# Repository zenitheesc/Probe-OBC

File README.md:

<h1 align="center" style="color:white; background-color:black">Probe-OBC</h1>
<h4 align="center">On-Board Computer for stratospheric probes, using Zenith Stack</h4>

<p align="center">

</p>

<p align="center">
    <a href="#environment-and-tools">Environment and Tools</a> •
    <a href="#z-hub">Z-Hub</a> •
    <a href="#matias-obc">Matias OBC</a>
</p>

This configuration of the Eletrical power system requires a board that monitors the charger and battery, in addition to performing thermal control.

## Environment and tools

This system was designed using Eagle v.9.4.2

## Z-Hub

<a href="https://github.com/zenitheesc/Probe-OBC/tree/main/Hardware/Matias_OBC-v.3.0"><h2>Matias OBC</h2></a>

---

<p align="center">

</p>
<p align = "center">
<a href="zenith.eesc@gmail.com">zenith.eesc@gmail.com</a>
</p>

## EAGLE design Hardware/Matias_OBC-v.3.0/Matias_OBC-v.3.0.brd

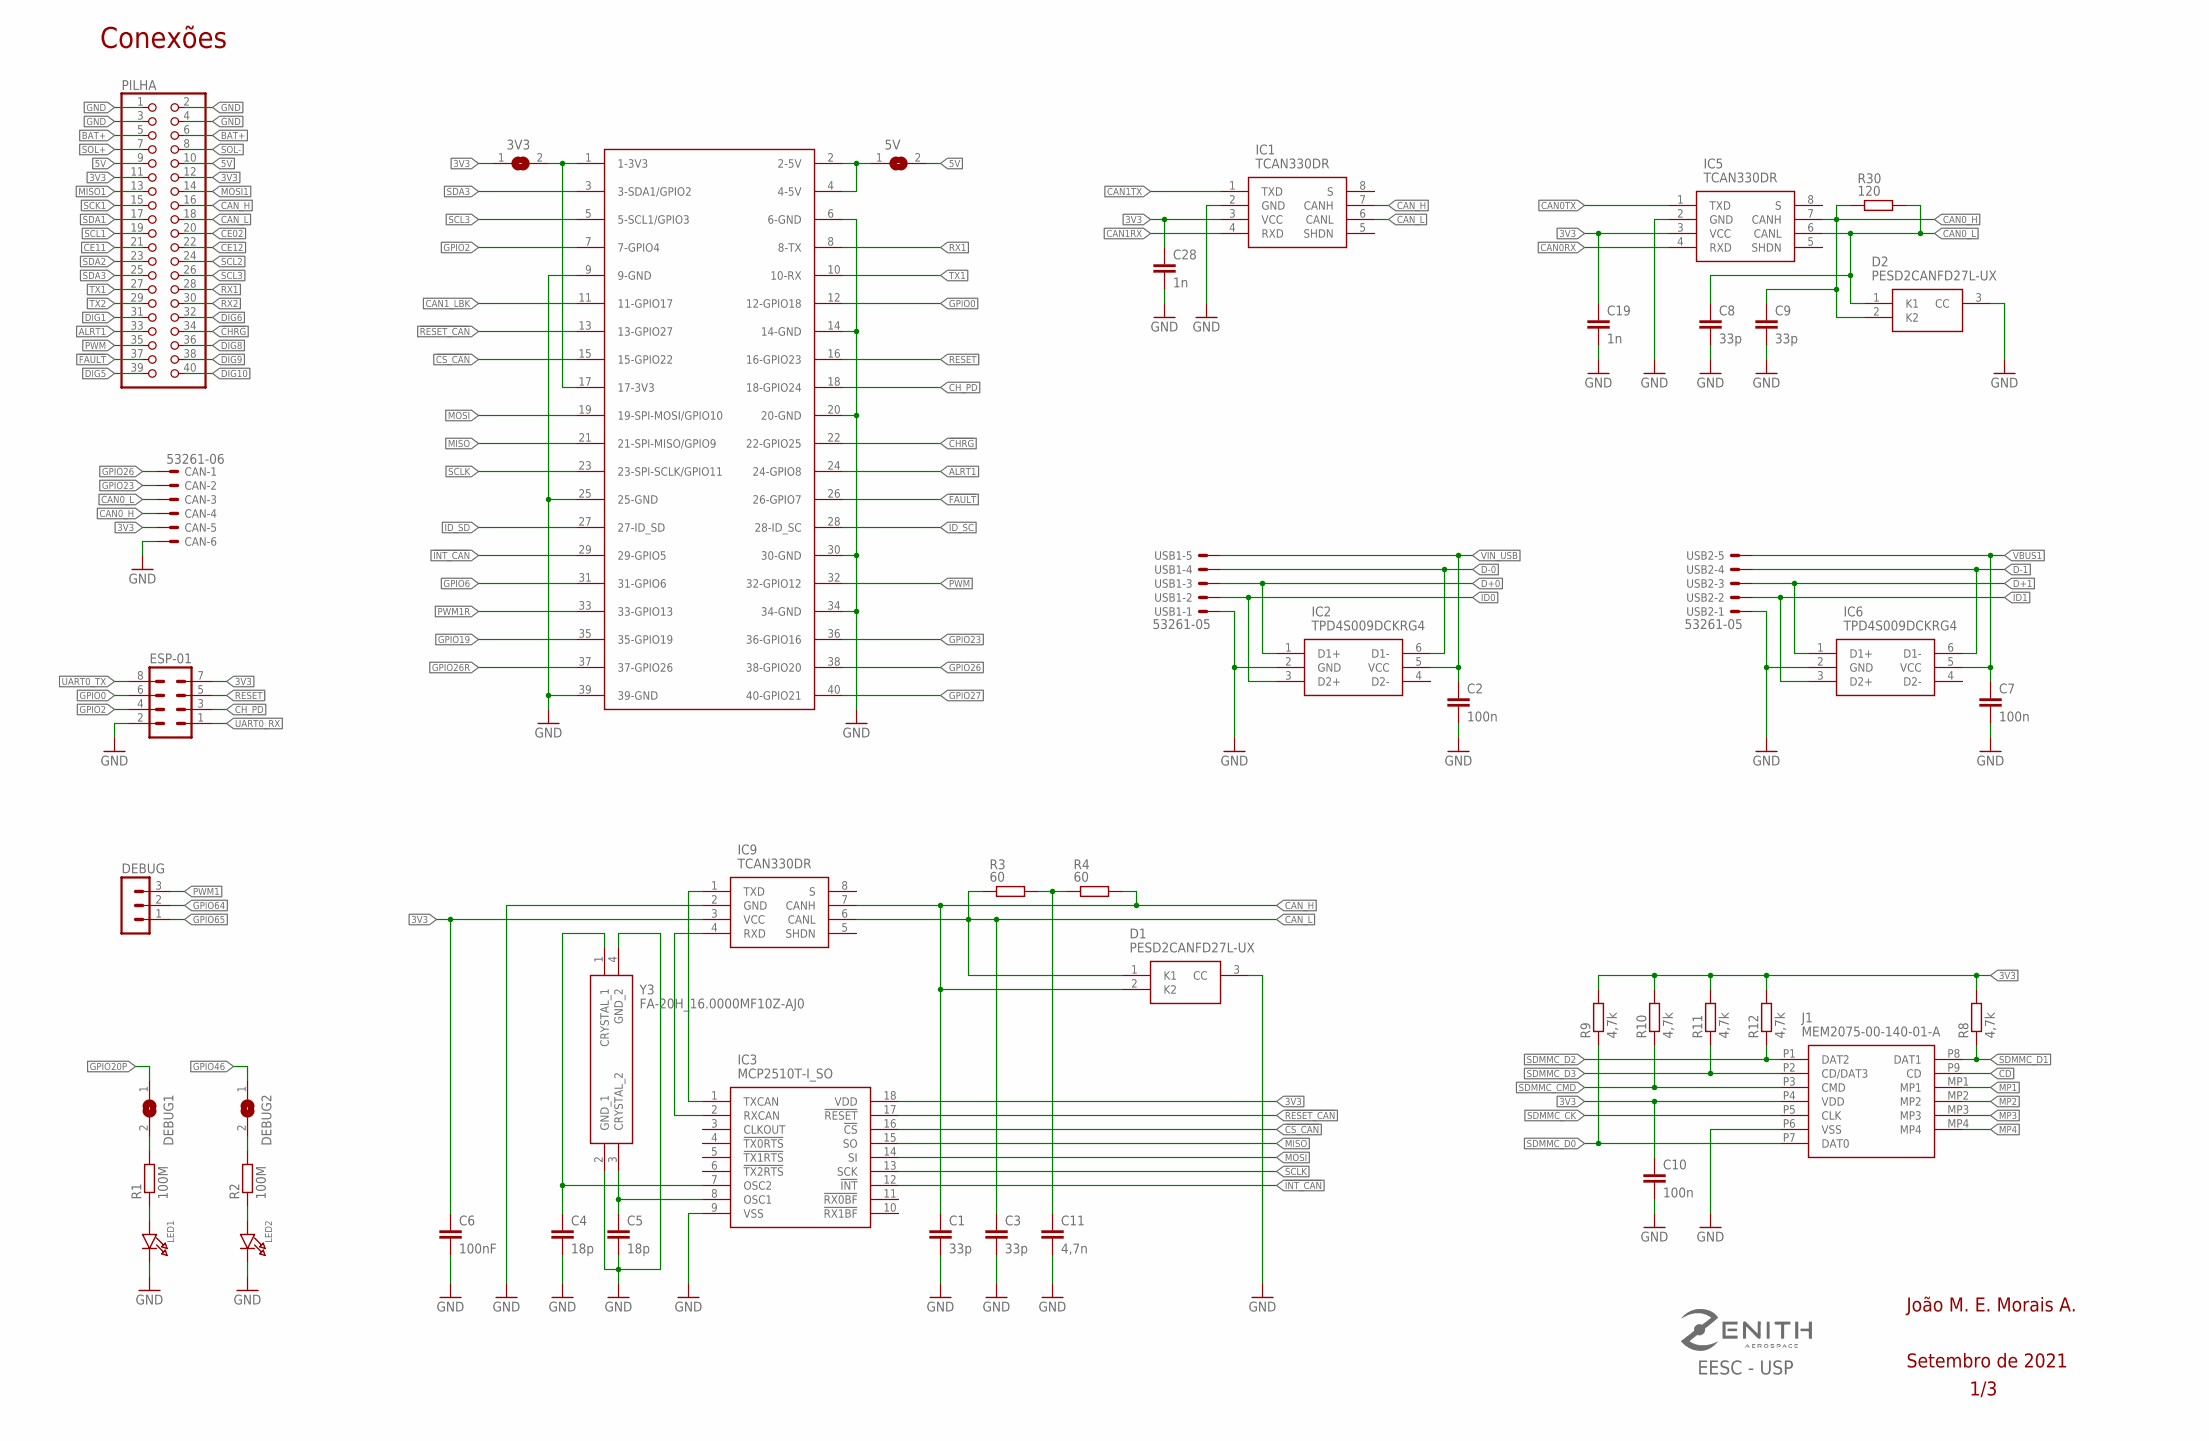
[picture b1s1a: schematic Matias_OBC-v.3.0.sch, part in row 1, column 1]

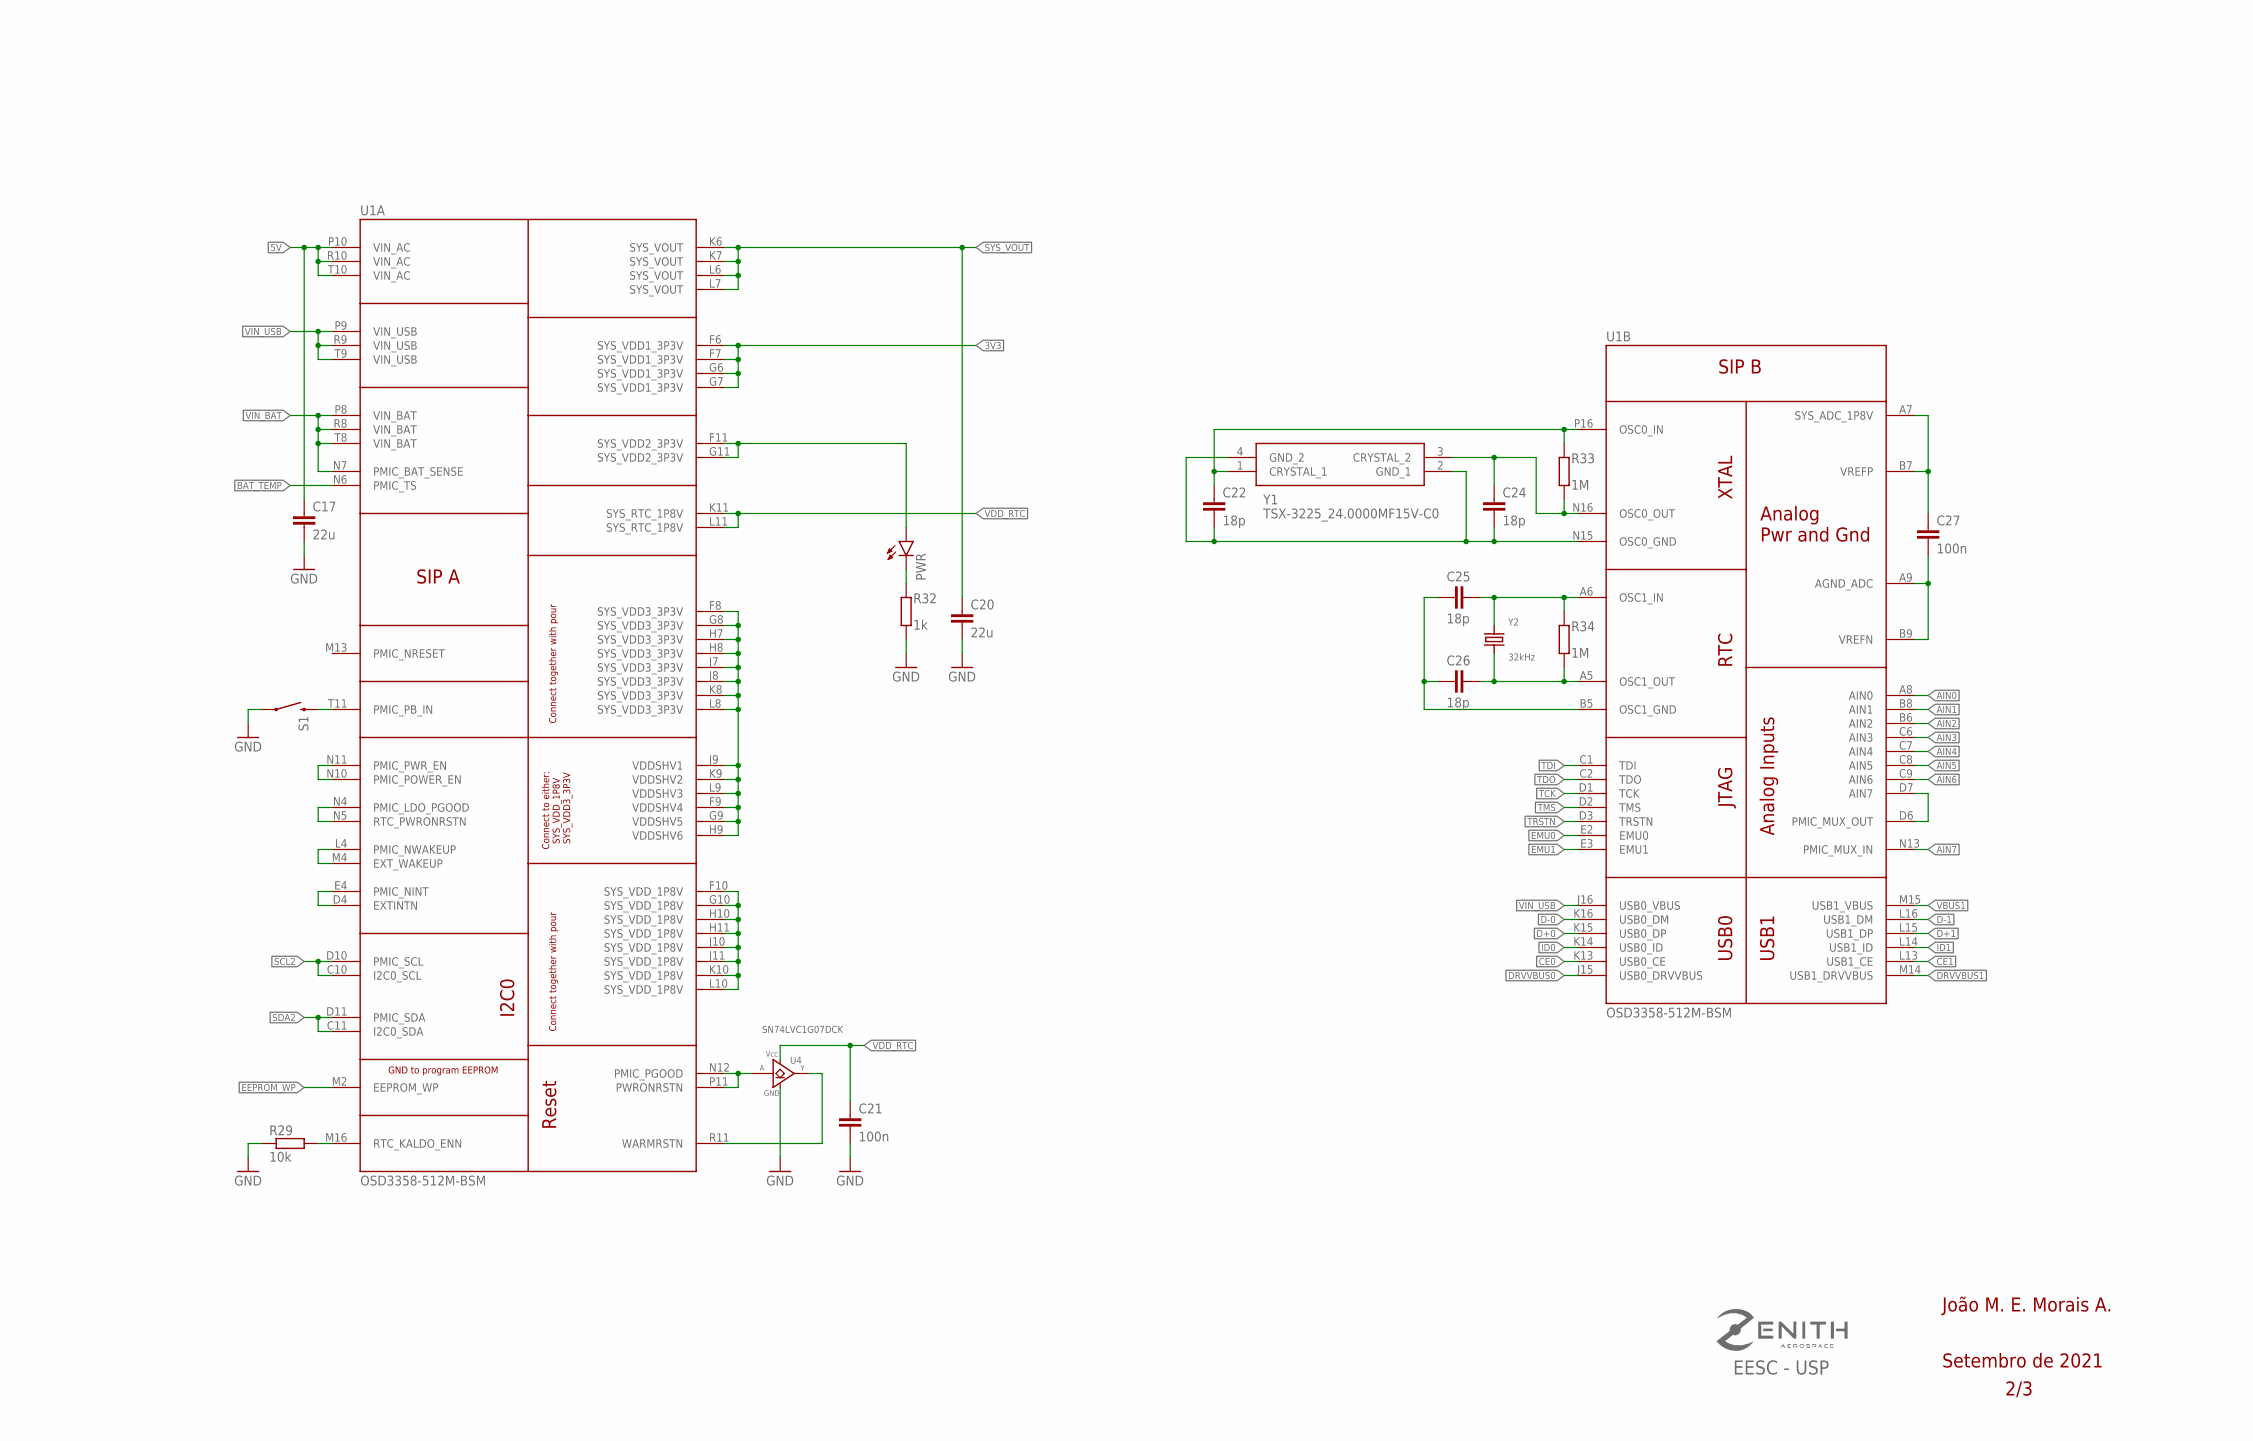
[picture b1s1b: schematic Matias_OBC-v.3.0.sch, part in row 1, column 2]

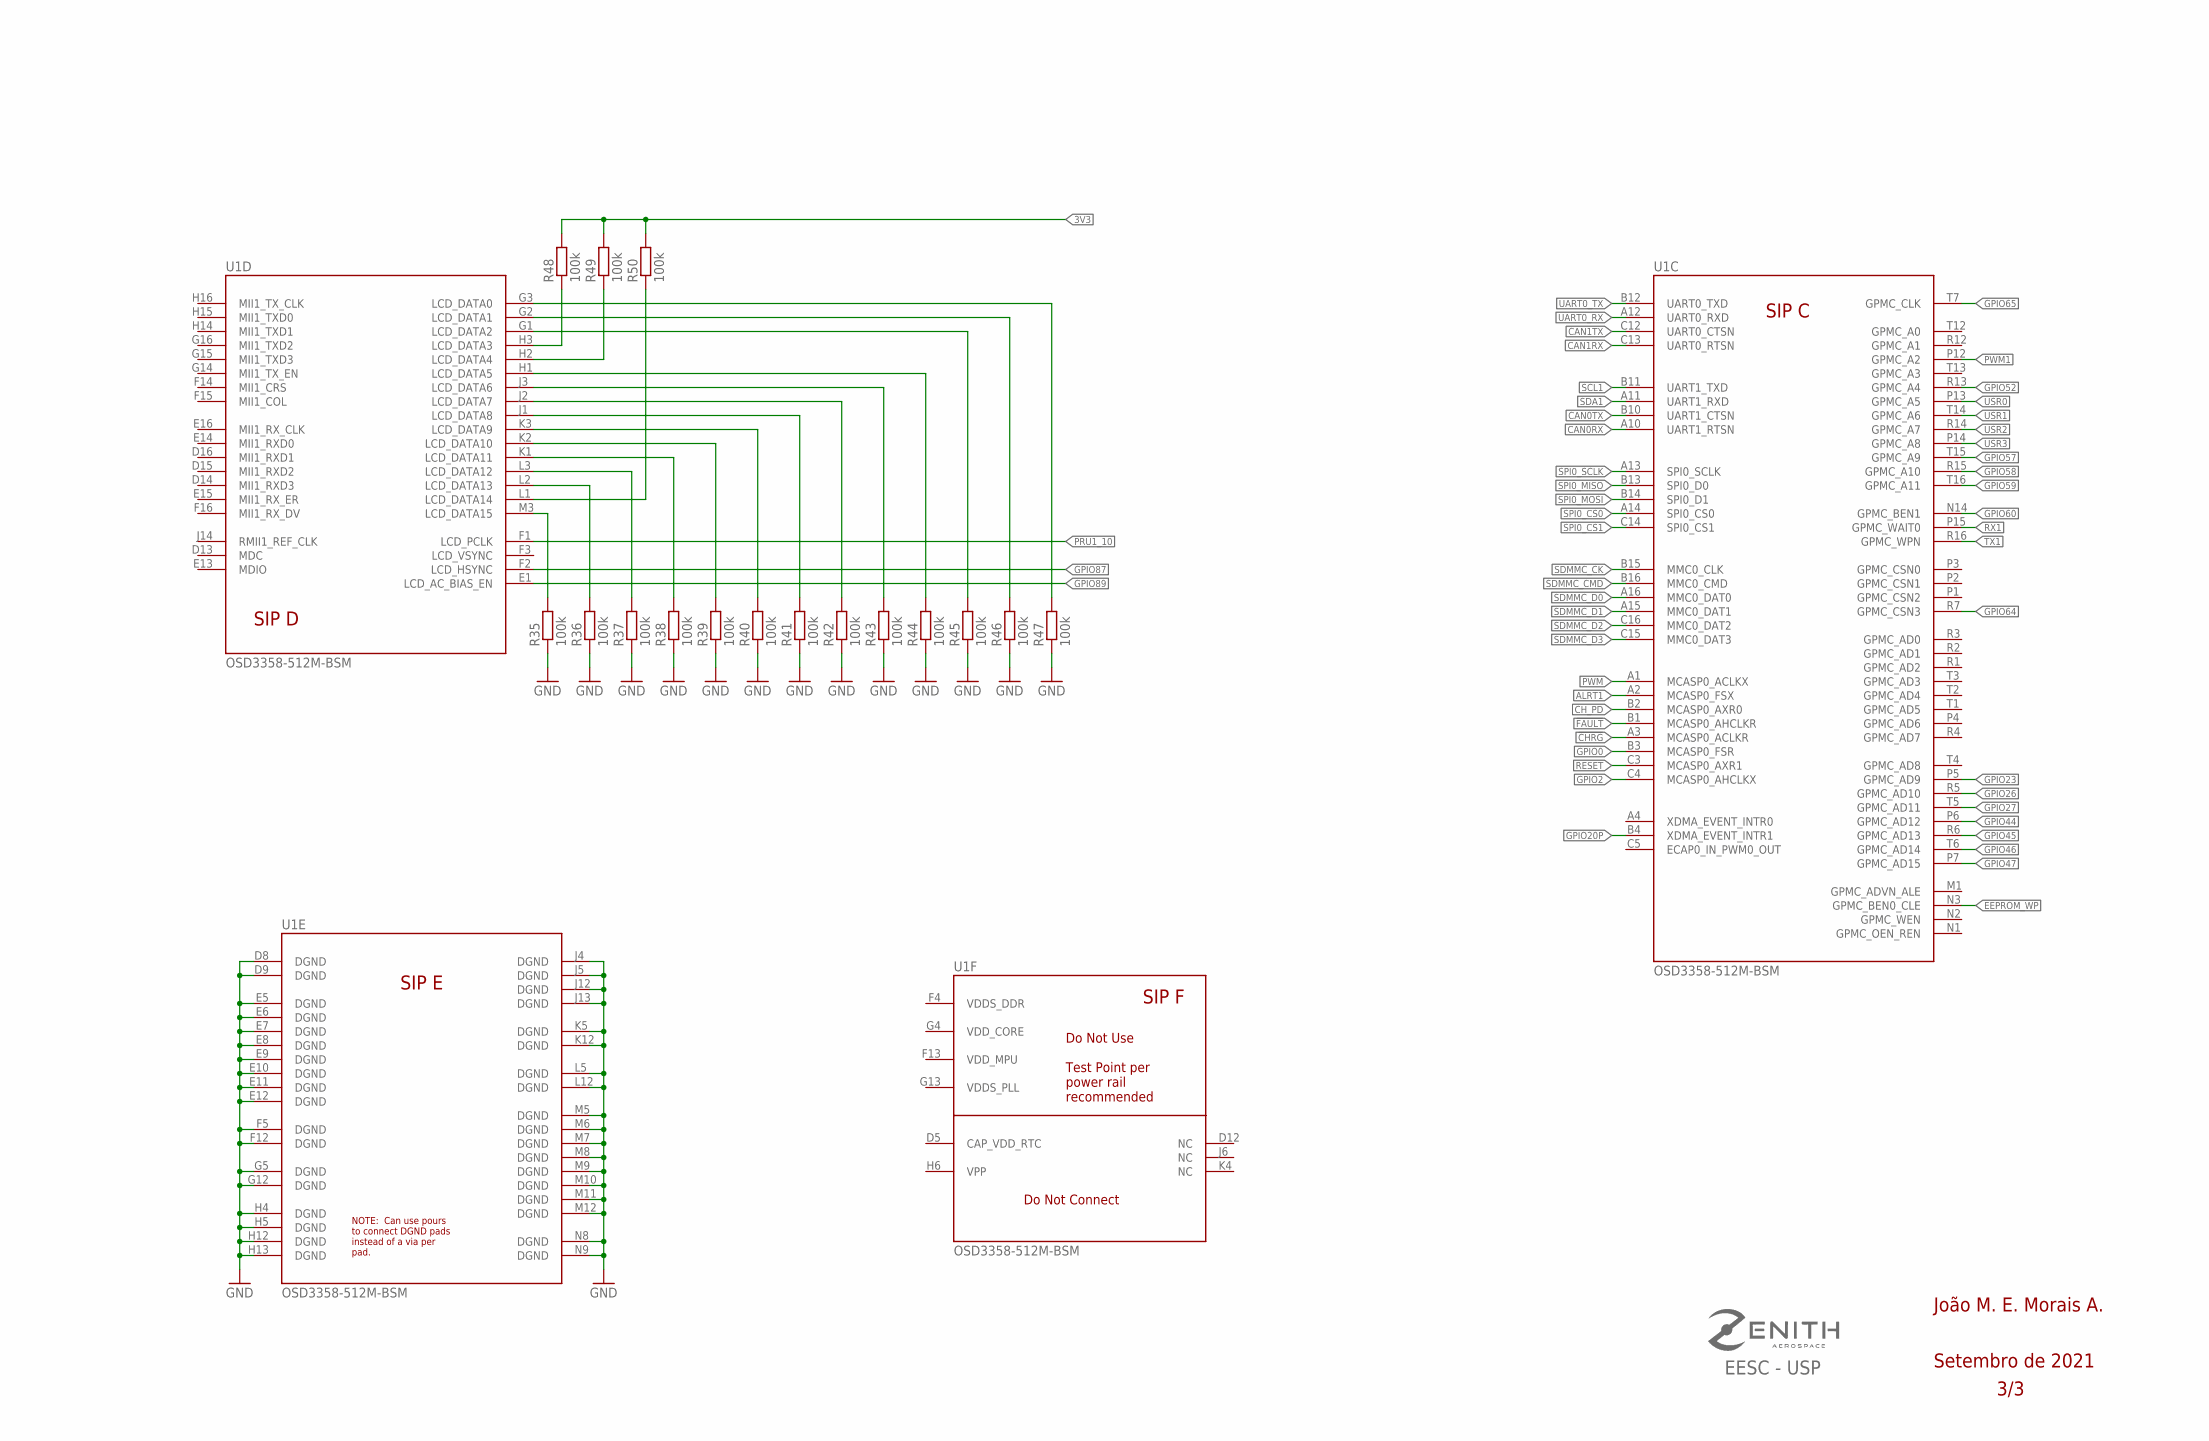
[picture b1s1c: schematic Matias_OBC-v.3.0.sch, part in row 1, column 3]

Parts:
3V3, 5V: SJ
C1, C3, C8, C9: 33p; C0805
C2, C7, C10, C21, C27: 100n; C0805
C4, C5, C22, C24, C25, C26: 18p; C0805
C6: 100nF; C0805
C11: 4,7n; C0805
C17, C20: 22u; C0805
C19, C28: 1n; C0805
CAN: 53261-06
D1, D2: PESD2CANFD27L-UX; SOT65P210X110-3N
DEBUG: MA03-1
DEBUG1, DEBUG2: SOLDERJUMPERREFLOW_NOPASTE; SOLDERJUMPER_REFLOW_NOPASTE
ESP-01: MA04-2
IC1, IC5, IC9: TCAN330DR; SOIC127P600X175-8N
IC2, IC6: TPD4S009DCKRG4; SOT65P210X110-6N
IC3: MCP2510T-I_SO; SOIC127P1030X265-18N
J1: MEM2075-00-140-01-A; MEM20750014001A
LED1, LED2: LED1206; CHIPLED_1206
PILHA: PINHD-2X20; 2X20
PWR: LEDCHIP-LED0805; CHIP-LED0805
R1, R2: 100M; R0805
R3, R4: 60; R0805
R8, R9, R10, R11, R12: 4,7k; R0805
R29: 10k; R0805
R30: 120; R0805
R32: 1k; R0805
R33, R34: 1M; R0805
R35, R36, R37, R38, R39, R40, R41, R42, R43, R44, R45, R46, R47, R48, R49, R50: 100k; R0805
S1: MOMENTARY-SWITCH-SPST-SMD-6.0X3.5MM; TACTILE_SWITCH_SMD_6.0X3.5MM
U1: OSD3358-512M-BSM; OSD335X-BGA-256
U2: RASPBERRY-PI+PIZERO; RASPBERRY-PI-ZERO
U4: SN74LVC1G07DCK; SC70(TI-DCK)
USB1, USB2: 53261-05
Y1: TSX-3225_24.0000MF15V-C0; TSX3225240000MF15VC0
Y2: 32kHz; CRYSTAL_8X3.8
Y3: FA-20H_16.0000MF10Z-AJ0; FA20H160000MF12ZAC3

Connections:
3V3: 3V3.1, C6.1, C10.1, C19.1, C28.1, CAN.5, ESP-01.7, IC1.3 (VCC), IC3.18 (VDD), IC5.3 (VCC), IC9.3 (VCC), J1.P4 (VDD), PILHA.11, PILHA.12, R8.2, R9.2, R10.2, R11.2, R12.2, R48.2, R49.2, R50.2, U1.F6 (SYS_VDD1_3P3V), U1.F7 (SYS_VDD1_3P3V), U1.G6 (SYS_VDD1_3P3V), U1.G7 (SYS_VDD1_3P3V)
5V: 5V.2, C17.1, PILHA.9, PILHA.10, U1.P10 (VIN_AC), U1.R10 (VIN_AC), U1.T10 (VIN_AC)
!CHRG: PILHA.34, U1.A3 (MCASP0_ACLKR), U2.22 (22-GPIO25)
!CS_CAN: IC3.16 (!CS), U2.15 (15-GPIO22)
!FAULT: PILHA.37, U1.B1 (MCASP0_AHCLKR), U2.26 (26-GPIO7)
!INT_CAN: IC3.12 (!INT), U2.29 (29-GPIO5)
!RESET_CAN: IC3.17 (!RESET), U2.13 (13-GPIO27)
AIN0: U1.A8 (AIN0)
AIN1: U1.B8 (AIN1)
AIN2: U1.B6 (AIN2)
AIN3: U1.C6 (AIN3)
AIN4: U1.C7 (AIN4)
AIN5: U1.C8 (AIN5)
AIN6: U1.C9 (AIN6)
AIN7: U1.N13 (PMIC_MUX_IN)
ALRT1: PILHA.33, U1.A2 (MCASP0_FSX), U2.24 (24-GPIO8)
BAT+: PILHA.5, PILHA.6
BAT_TEMP: U1.N6 (PMIC_TS)
CAN0RX: IC5.4 (RXD), U1.A10 (UART1_RTSN)
CAN0TX: IC5.1 (TXD), U1.B10 (UART1_CTSN)
CAN0_H: C9.1, CAN.4, D2.2 (K2), IC5.7 (CANH), R30.1
CAN0_L: C8.1, CAN.3, D2.1 (K1), IC5.6 (CANL), R30.2
CAN1RX: IC1.4 (RXD), U1.C13 (UART0_RTSN)
CAN1TX: IC1.1 (TXD), U1.C12 (UART0_CTSN)
CAN1_LBK: U2.11 (11-GPIO17)
CAN_H: C1.1, D1.2 (K2), IC1.7 (CANH), IC9.7 (CANH), PILHA.16, R4.1
CAN_L: C3.1, D1.1 (K1), IC1.6 (CANL), IC9.6 (CANL), PILHA.18, R3.2
CD: J1.P9 (CD)
CE0: U1.K13 (USB0_CE)
CE1: U1.L13 (USB1_CE)
CE02: PILHA.20
CE11: PILHA.21
CE12: PILHA.22
CH_PD: ESP-01.3, U1.B2 (MCASP0_AXR0), U2.18 (18-GPIO24)
D+0: IC2.1 (D1+), U1.K15 (USB0_DP), USB1.3
D+1: IC6.1 (D1+), U1.L15 (USB1_DP), USB2.3
D-0: IC2.6 (D1-), U1.K16 (USB0_DM), USB1.4
D-1: IC6.6 (D1-), U1.L16 (USB1_DM), USB2.4
DIG1: PILHA.31
DIG5: PILHA.39
DIG6: PILHA.32
DIG8: PILHA.36
DIG9: PILHA.38
DIG10: PILHA.40
DRVVBUS0: U1.J15 (USB0_DRVVBUS)
DRVVBUS1: U1.M14 (USB1_DRVVBUS)
EEPROM_WP: U1.M2 (EEPROM_WP), U1.N3 (GPMC_BEN0_CLE)
EMU0: U1.E2 (EMU0)
EMU1: U1.E3 (EMU1)
GND: C1.2, C2.2, C3.2, C4.2, C5.2, C6.2, C7.2, C8.2, C9.2, C10.2, C11.2, C17.2, C19.2, C20.2, C21.2, C28.2, CAN.6, D1.3 (CC), D2.3 (CC), ESP-01.2, IC1.2 (GND), IC2.2 (GND), IC3.9 (VSS), IC5.2 (GND), IC6.2 (GND), IC9.2 (GND), J1.P6 (VSS), LED1.C, LED2.C, PILHA.1, PILHA.2, PILHA.3, PILHA.4, R29.1, R32.1, R35.1, R36.1, R37.1, R38.1, R39.1, R40.1, R41.1, R42.1, R43.1, R44.1, R45.1, R46.1, R47.1, S1.1, U1.D8 (DGND), U1.D9 (DGND), U1.E5 (DGND), U1.E6 (DGND), U1.E7 (DGND), U1.E8 (DGND), U1.E9 (DGND), U1.E10 (DGND), U1.E11 (DGND), U1.E12 (DGND), U1.F5 (DGND), U1.F12 (DGND), U1.G5 (DGND), U1.G12 (DGND), U1.H4 (DGND), U1.H5 (DGND), U1.H12 (DGND), U1.H13 (DGND), U1.J4 (DGND), U1.J5 (DGND), U1.J12 (DGND), U1.J13 (DGND), U1.K5 (DGND), U1.K12 (DGND), U1.L5 (DGND), U1.L12 (DGND), U1.M5 (DGND), U1.M6 (DGND), U1.M7 (DGND), U1.M8 (DGND), U1.M9 (DGND), U1.M10 (DGND), U1.M11 (DGND), U1.M12 (DGND), U1.N8 (DGND), U1.N9 (DGND), U2.6 (6-GND), U2.9 (9-GND), U2.14 (14-GND), U2.20 (20-GND), U2.25 (25-GND), U2.30 (30-GND), U2.34 (34-GND), U2.39 (39-GND), U4.3 (GND), USB1.1, USB2.1, Y3.2 (GND_1), Y3.4 (GND_2)
GPIO0: ESP-01.6, U1.B3 (MCASP0_FSR), U2.12 (12-GPIO18)
GPIO2: ESP-01.4, U1.C4 (MCASP0_AHCLKX), U2.7 (7-GPIO4)
GPIO6: U2.31 (31-GPIO6)
GPIO19: U2.35 (35-GPIO19)
GPIO20P: DEBUG1.1, U1.B4 (XDMA_EVENT_INTR1)
GPIO23: CAN.2, U1.P5 (GPMC_AD9), U2.36 (36-GPIO16)
GPIO26: CAN.1, U1.R5 (GPMC_AD10), U2.38 (38-GPIO20)
GPIO26R: U2.37 (37-GPIO26)
GPIO27: U1.T5 (GPMC_AD11), U2.40 (40-GPIO21)
GPIO44: U1.P6 (GPMC_AD12)
GPIO45: U1.R6 (GPMC_AD13)
GPIO46: DEBUG2.1, U1.T6 (GPMC_AD14)
GPIO47: U1.P7 (GPMC_AD15)
GPIO52: U1.R13 (GPMC_A4)
GPIO57: U1.T15 (GPMC_A9)
GPIO58: U1.R15 (GPMC_A10)
GPIO59: U1.T16 (GPMC_A11)
GPIO60: U1.N14 (GPMC_BEN1)
GPIO64: DEBUG.2, U1.R7 (GPMC_CSN3)
GPIO65: DEBUG.1, U1.T7 (GPMC_CLK)
GPIO87: U1.F2 (LCD_HSYNC)
GPIO89: U1.E1 (LCD_AC_BIAS_EN)
ID0: IC2.3 (D2+), U1.K14 (USB0_ID), USB1.2
ID1: IC6.3 (D2+), U1.L14 (USB1_ID), USB2.2
ID_SC: U2.28 (28-ID_SC)
ID_SD: U2.27 (27-ID_SD)
MISO: IC3.15 (SO), U2.21 (21-SPI-MISO/GPIO9)
MISO1: PILHA.13
MOSI: IC3.14 (SI), U2.19 (19-SPI-MOSI/GPIO10)
MOSI1: PILHA.14
MP1: J1.MP1
MP2: J1.MP2
MP3: J1.MP3
MP4: J1.MP4
unnamed: LED1.A, R1.1
unnamed: 5V.1, U2.2 (2-5V), U2.4 (4-5V)
unnamed: 3V3.2, U2.1 (1-3V3), U2.17 (17-3V3)
unnamed: C11.1, R3.1, R4.2
unnamed: LED2.A, R2.1
unnamed: DEBUG1.2, R1.2
unnamed: DEBUG2.2, R2.2
unnamed: C5.1, IC3.8 (OSC1), Y3.3 (CRYSTAL_2)
unnamed: C4.1, IC3.7 (OSC2), Y3.1 (CRYSTAL_1)
unnamed: S1.2, U1.T11 (PMIC_PB_IN)
unnamed: U1.N10 (PMIC_POWER_EN), U1.N11 (PMIC_PWR_EN)
unnamed: U1.N4 (PMIC_LDO_PGOOD), U1.N5 (RTC_PWRONRSTN)
unnamed: U1.L4 (PMIC_NWAKEUP), U1.M4 (EXT_WAKEUP)
unnamed: U1.D4 (EXTINTN), U1.E4 (PMIC_NINT)
unnamed: R29.2, U1.M16 (RTC_KALDO_ENN)
unnamed: PWR.A, U1.F11 (SYS_VDD2_3P3V), U1.G11 (SYS_VDD2_3P3V)
unnamed: PWR.C, R32.2
unnamed: U1.F8 (SYS_VDD3_3P3V), U1.F9 (VDDSHV4), U1.G8 (SYS_VDD3_3P3V), U1.G9 (VDDSHV5), U1.H7 (SYS_VDD3_3P3V), U1.H8 (SYS_VDD3_3P3V), U1.H9 (VDDSHV6), U1.J7 (SYS_VDD3_3P3V), U1.J8 (SYS_VDD3_3P3V), U1.J9 (VDDSHV1), U1.K8 (SYS_VDD3_3P3V), U1.K9 (VDDSHV2), U1.L8 (SYS_VDD3_3P3V), U1.L9 (VDDSHV3)
unnamed: U1.F10 (SYS_VDD_1P8V), U1.G10 (SYS_VDD_1P8V), U1.H10 (SYS_VDD_1P8V), U1.H11 (SYS_VDD_1P8V), U1.J10 (SYS_VDD_1P8V), U1.J11 (SYS_VDD_1P8V), U1.K10 (SYS_VDD_1P8V), U1.L10 (SYS_VDD_1P8V)
unnamed: U1.N12 (PMIC_PGOOD), U1.P11 (PWRONRSTN), U4.2 (A)
unnamed: U1.R11 (WARMRSTN), U4.4 (Y)
unnamed: C22.1, R33.2, U1.P16 (OSC0_IN), Y1.1 (CRYSTAL_1)
unnamed: C24.1, R33.1, U1.N16 (OSC0_OUT), Y1.3 (CRYSTAL_2)
unnamed: C22.2, C24.2, U1.N15 (OSC0_GND), Y1.2 (GND_1), Y1.4 (GND_2)
unnamed: C26.1, R34.1, U1.A5 (OSC1_OUT), Y2.P$4 (2)
unnamed: C25.1, R34.2, U1.A6 (OSC1_IN), Y2.P$1 (1)
unnamed: C25.2, C26.2, U1.B5 (OSC1_GND)
unnamed: U1.D6 (PMIC_MUX_OUT), U1.D7 (AIN7)
unnamed: C27.2, U1.A9 (AGND_ADC), U1.B9 (VREFN)
unnamed: C27.1, U1.A7 (SYS_ADC_1P8V), U1.B7 (VREFP)
unnamed: R35.2, U1.M3 (LCD_DATA15)
unnamed: R36.2, U1.L2 (LCD_DATA13)
unnamed: R37.2, U1.L3 (LCD_DATA12)
unnamed: R38.2, U1.K1 (LCD_DATA11)
unnamed: R39.2, U1.K2 (LCD_DATA10)
unnamed: R40.2, U1.K3 (LCD_DATA9)
unnamed: R41.2, U1.J1 (LCD_DATA8)
unnamed: R42.2, U1.J2 (LCD_DATA7)
unnamed: R43.2, U1.J3 (LCD_DATA6)
unnamed: R44.2, U1.H1 (LCD_DATA5)
unnamed: R45.2, U1.G1 (LCD_DATA2)
unnamed: R46.2, U1.G2 (LCD_DATA1)
unnamed: R47.2, U1.G3 (LCD_DATA0)
unnamed: R48.1, U1.H3 (LCD_DATA3)
unnamed: R49.1, U1.H2 (LCD_DATA4)
unnamed: R50.1, U1.L1 (LCD_DATA14)
PRU1_10: U1.F1 (LCD_PCLK)
PWM: PILHA.35, U1.A1 (MCASP0_ACLKX), U2.32 (32-GPIO12)
PWM1: DEBUG.3, U1.P12 (GPMC_A2)
PWM1R: U2.33 (33-GPIO13)
RESET: ESP-01.5, U1.C3 (MCASP0_AXR1), U2.16 (16-GPIO23)
RX1: PILHA.28, U1.P15 (GPMC_WAIT0), U2.8 (8-TX)
RX2: PILHA.30
RXCAN1: IC3.2 (RXCAN), IC9.4 (RXD)
SCK1: PILHA.15
SCL1: PILHA.19, U1.B11 (UART1_TXD)
SCL2: PILHA.24, U1.C10 (I2C0_SCL), U1.D10 (PMIC_SCL)
SCL3: PILHA.26, U2.5 (5-SCL1/GPIO3)
SCLK: IC3.13 (SCK), U2.23 (23-SPI-SCLK/GPIO11)
SDA1: PILHA.17, U1.A11 (UART1_RXD)
SDA2: PILHA.23, U1.C11 (I2C0_SDA), U1.D11 (PMIC_SDA)
SDA3: PILHA.25, U2.3 (3-SDA1/GPIO2)
SDMMC_CK: J1.P5 (CLK), U1.B15 (MMC0_CLK)
SDMMC_CMD: J1.P3 (CMD), R10.1, U1.B16 (MMC0_CMD)
SDMMC_D0: J1.P7 (DAT0), R9.1, U1.A16 (MMC0_DAT0)
SDMMC_D1: J1.P8 (DAT1), R8.1, U1.A15 (MMC0_DAT1)
SDMMC_D2: J1.P1 (DAT2), R12.1, U1.C16 (MMC0_DAT2)
SDMMC_D3: J1.P2 (CD/DAT3), R11.1, U1.C15 (MMC0_DAT3)
SOL+: PILHA.7
SOL-: PILHA.8
SPI0_CS0: U1.A14 (SPI0_CS0)
SPI0_CS1: U1.C14 (SPI0_CS1)
SPI0_MISO: U1.B13 (SPI0_D0)
SPI0_MOSI: U1.B14 (SPI0_D1)
SPI0_SCLK: U1.A13 (SPI0_SCLK)
SYS_VOUT: C20.1, U1.K6 (SYS_VOUT), U1.K7 (SYS_VOUT), U1.L6 (SYS_VOUT), U1.L7 (SYS_VOUT)
TCK: U1.D1 (TCK)
TDI: U1.C1 (TDI)
TDO: U1.C2 (TDO)
TMS: U1.D2 (TMS)
TRSTN: U1.D3 (TRSTN)
TX1: PILHA.27, U1.R16 (GPMC_WPN), U2.10 (10-RX)
TX2: PILHA.29
TXCAN1: IC3.1 (TXCAN), IC9.1 (TXD)
UART0_RX: ESP-01.1, U1.A12 (UART0_RXD)
UART0_TX: ESP-01.8, U1.B12 (UART0_TXD)
USR0: U1.P13 (GPMC_A5)
USR1: U1.T14 (GPMC_A6)
USR2: U1.R14 (GPMC_A7)
USR3: U1.P14 (GPMC_A8)
VBUS1: C7.1, IC6.5 (VCC), U1.M15 (USB1_VBUS), USB2.5
VDD_RTC: C21.1, U1.K11 (SYS_RTC_1P8V), U1.L11 (SYS_RTC_1P8V), U4.5 (VCC)
VIN_BAT: U1.N7 (PMIC_BAT_SENSE), U1.P8 (VIN_BAT), U1.R8 (VIN_BAT), U1.T8 (VIN_BAT)
VIN_USB: C2.1, IC2.5 (VCC), U1.J16 (USB0_VBUS), U1.P9 (VIN_USB), U1.R9 (VIN_USB), U1.T9 (VIN_USB), USB1.5

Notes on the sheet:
C:/Users/marcu/Desktop/Ensino Superior/Graduação - Eng Elétrica/Zenith/zenith-v2.bmp
EESC - USP
Setembro de 2021
1/3
João M. E. Morais A.
Conexões
2/3
3/3

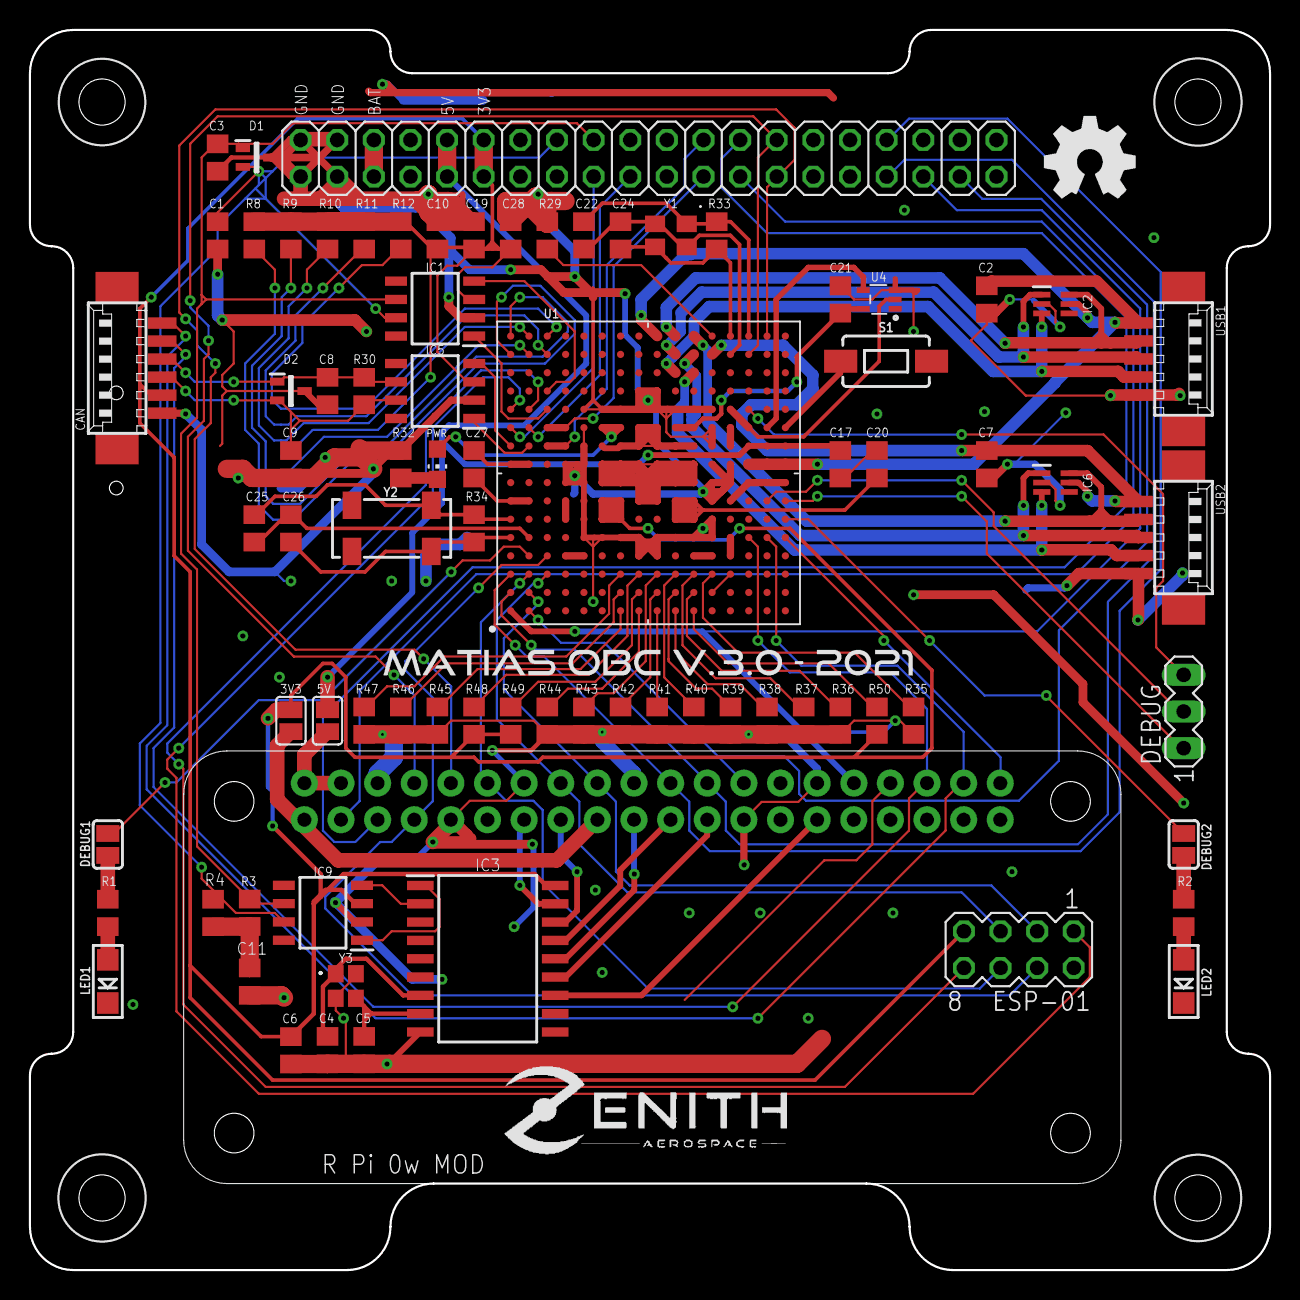
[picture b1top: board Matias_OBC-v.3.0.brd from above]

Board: 2 copper layers, 86.0 x 86.0 mm, 80 parts (1 on the bottom side), 110 nets.

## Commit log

2021-09-28 Rename [TEMPLATE]README.md to README.md

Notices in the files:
parts and their libraries:
SparkFun-Switches: Licensing: Creative Commons ShareAlike 4.0 International - https://creativecommons.org/licenses/by-sa/4.0
